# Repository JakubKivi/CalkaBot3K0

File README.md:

# CalkaBot3K0

Całkabot 3k0 is a mini-sumo robot equipped with arms designed to lift the opponent. Taking advantage of the lack of size restrictions after the round begins, this beauty you see in the picture unfolds its lifting arms. In the photo, it's already in the fully deployed position.

More info [here](https://jakubkivi.github.io#portfolio-modal-calk3)

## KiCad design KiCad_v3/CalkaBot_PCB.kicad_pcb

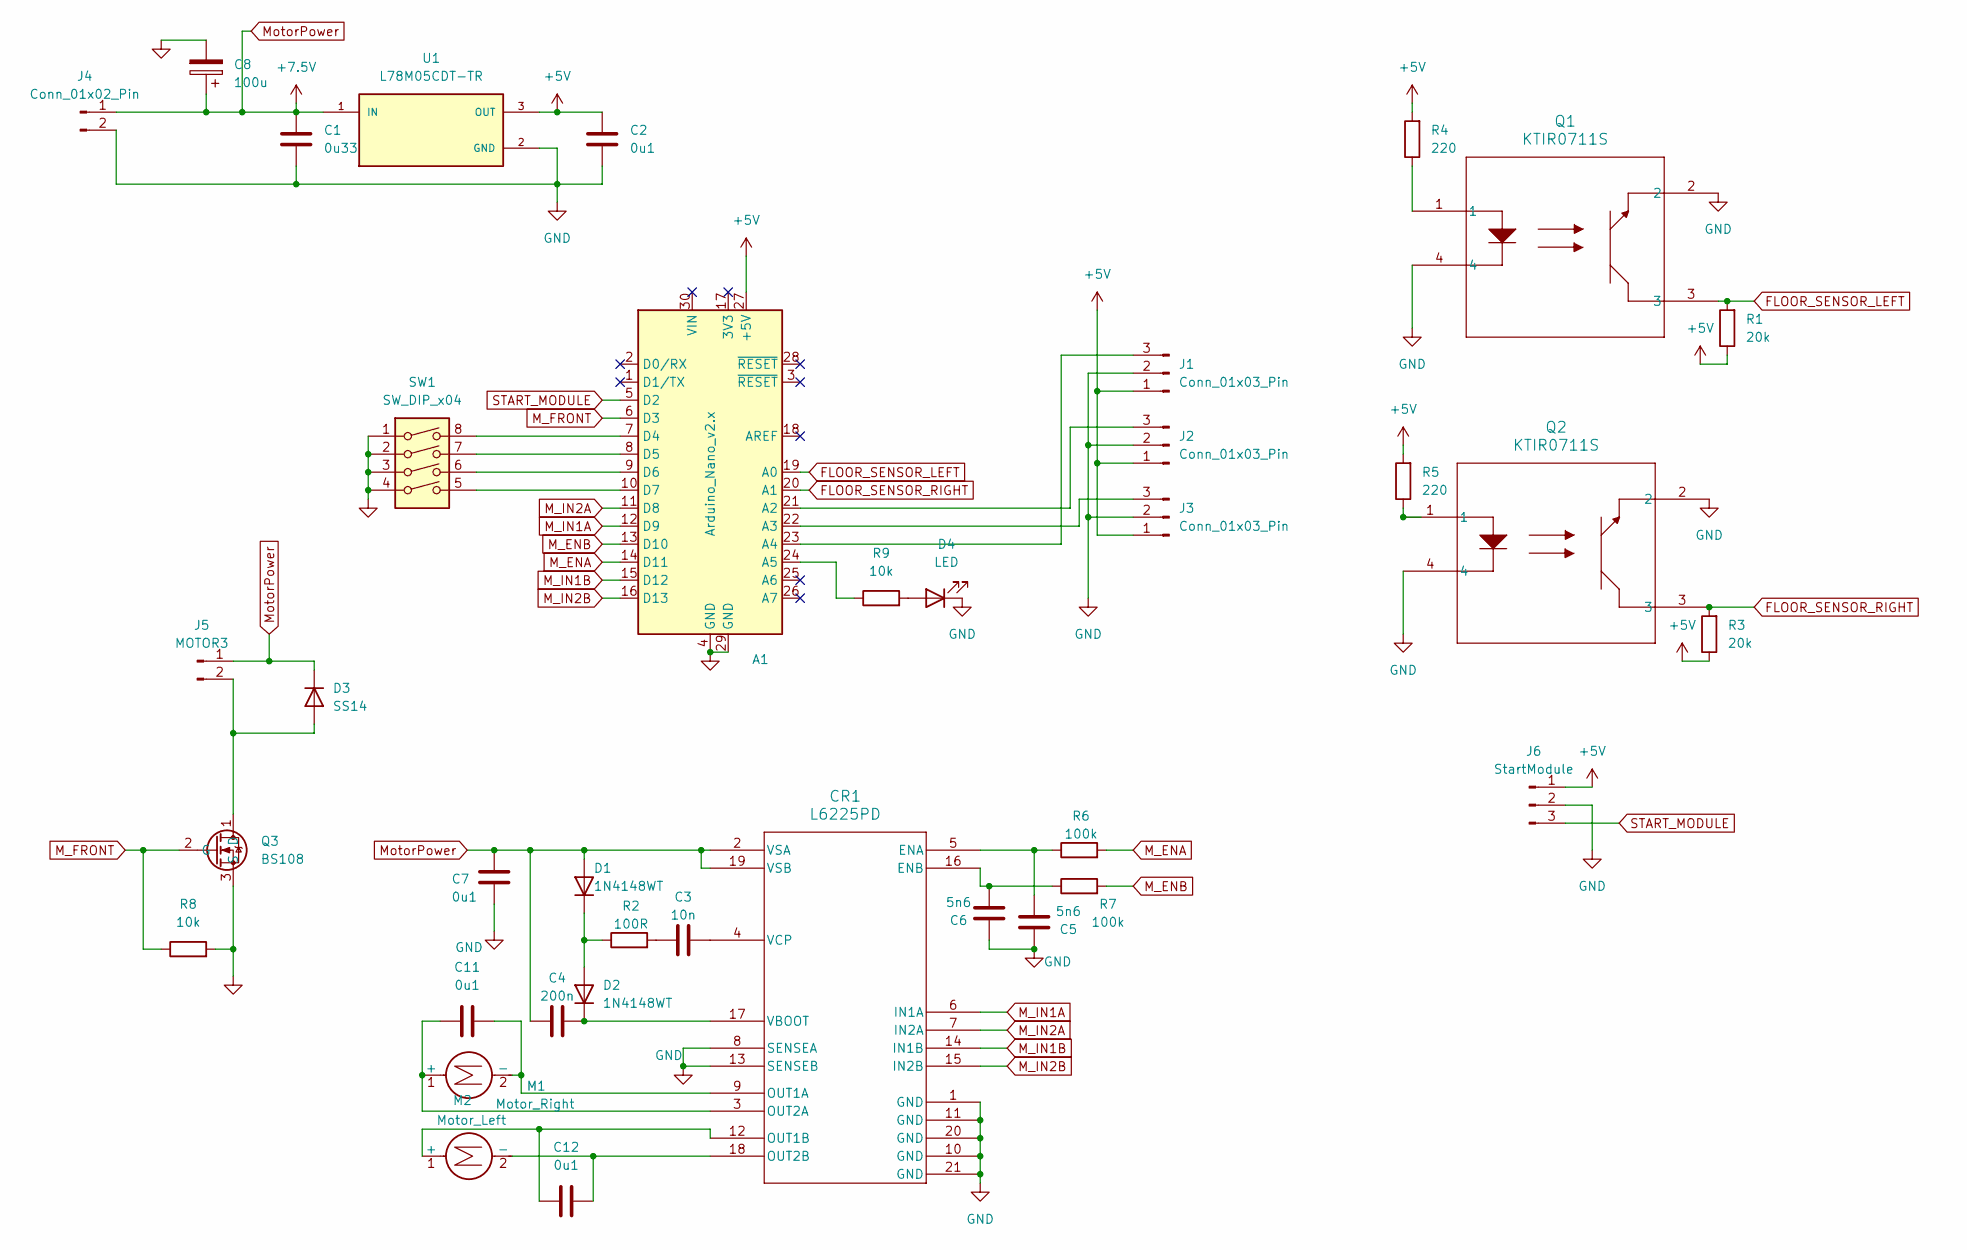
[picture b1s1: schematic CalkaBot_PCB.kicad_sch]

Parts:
A1: Arduino_Nano_v2.x; Arduino_Nano
C1: 0u33; C_0805_2012Metric_Pad1.18x1.45mm_HandSolder
C2, C7, C11, C12: 0u1; C_0805_2012Metric_Pad1.18x1.45mm_HandSolder
C3: 10n; C_0805_2012Metric_Pad1.18x1.45mm_HandSolder
C4: 200n; C_0805_2012Metric_Pad1.18x1.45mm_HandSolder
C5, C6: 5n6; C_0805_2012Metric_Pad1.18x1.45mm_HandSolder
C8: 100u; CP_Elec_6.3x7.7
CR1: L6225PD
D1, D2: 1N4148WT; D_SOD-123
D3: SS14; D_SMA_Handsoldering
D4: LED; LED_0805_2012Metric_Pad1.15x1.40mm_HandSolder
J1, J2, J3: Conn_01x03_Pin; JST_PH_B3B-PH-K_1x03_P2.00mm_Vertical
J4: Conn_01x02_Pin; PinHeader_1x02_P2.54mm_Vertical
J5: MOTOR3; PinHeader_1x02_P2.54mm_Vertical
J6: StartModule; PinHeader_1x03_P2.54mm_Vertical
M1: Motor_Right; CalkBot3k0_Motor_Right
M2: Motor_Left; CalkBot3k0_Motor_Left
Q1, Q2: KTIR0711S
Q3: BS108; SOT-223-IRLL014NTRPBF
R1, R3: 20k; R_0805_2012Metric_Pad1.20x1.40mm_HandSolder
R2: 100R; R_0805_2012Metric_Pad1.20x1.40mm_HandSolder
R4, R5: 220; R_0805_2012Metric_Pad1.20x1.40mm_HandSolder
R6, R7: 100k; R_0805_2012Metric_Pad1.20x1.40mm_HandSolder
R8, R9: 10k; R_0805_2012Metric_Pad1.20x1.40mm_HandSolder
SW1: SW_DIP_x04; SW_DIP_SPSTx04_Slide_9.78x12.34mm_W7.62mm_P2.54mm
U1: L78M05CDT-TR; VREG_L78M05CDT-TR; PARTREV 24

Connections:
+5V: A1.27 (+5V), C2.1, J1.1, J2.1, J3.1, J6.1, R1.1, R3.1, R4.2, R5.2, U1.3 (OUT)
FLOOR_SENSOR_LEFT: A1.19 (A0), Q1.3, R1.2
FLOOR_SENSOR_RIGHT: A1.20 (A1), Q2.3, R3.2
GND: A1.4 (GND), A1.29 (GND), C1.2, C2.2, C5.1, C6.1, C7.2, C8.2, CR1.1 (GND), CR1.8 (SENSEA), CR1.10 (GND), CR1.11 (GND), CR1.13 (SENSEB), CR1.20 (GND), CR1.21 (GND), D4.1 (K), J1.2, J2.2, J3.2, J4.2, J6.2, Q1.2, Q1.4, Q2.2, Q2.4, Q3.3 (S), R8.2, SW1.1, SW1.2, SW1.3, SW1.4, U1.2 (GND); also elsewhere on the board
M_ENA: A1.14 (D11), R6.2
M_ENB: A1.13 (D10), R7.2
M_FRONT: A1.6 (D3), Q3.2 (G), R8.1
M_IN1A: A1.12 (D9), CR1.6 (IN1A)
M_IN1B: A1.15 (D12), CR1.14 (IN1B)
M_IN2A: A1.11 (D8), CR1.7 (IN2A)
M_IN2B: A1.16 (D13), CR1.15 (IN2B)
MotorPower: C1.1, C4.1, C7.1, C8.1, CR1.2 (VSA), CR1.19 (VSB), D1.2 (A), D3.1 (K), J4.1, J5.1, U1.1 (IN); also elsewhere on the board
unnamed: A1.21 (A2), J2.3
unnamed: A1.22 (A3), J3.3
unnamed: A1.23 (A4), J1.3
unnamed: A1.24 (A5), R9.1
unnamed: A1.7 (D4), SW1.8
unnamed: A1.8 (D5), SW1.7
unnamed: A1.9 (D6), SW1.6
unnamed: A1.10 (D7), SW1.5
unnamed: C3.1, R2.2
unnamed: C5.2, CR1.5 (ENA), R6.1
unnamed: C6.2, CR1.16 (ENB), R7.1
unnamed: C11.1, CR1.9 (OUT1A), M1.2 (-)
unnamed: C12.2, CR1.12 (OUT1B), M2.1 (+)
unnamed: C11.2, CR1.3 (OUT2A), M1.1 (+)
unnamed: C12.1, CR1.18 (OUT2B), M2.2 (-)
unnamed: C4.2, CR1.17 (VBOOT), D2.1 (K)
unnamed: C3.2, CR1.4 (VCP)
unnamed: D1.1 (K), D2.2 (A), R2.1
unnamed: D3.2 (A), J5.2, Q3.1 (D)
unnamed: D4.2 (A), R9.2
unnamed: Q1.1, R4.1
unnamed: Q2.1, R5.1
START_MODULE: A1.5 (D2), J6.3

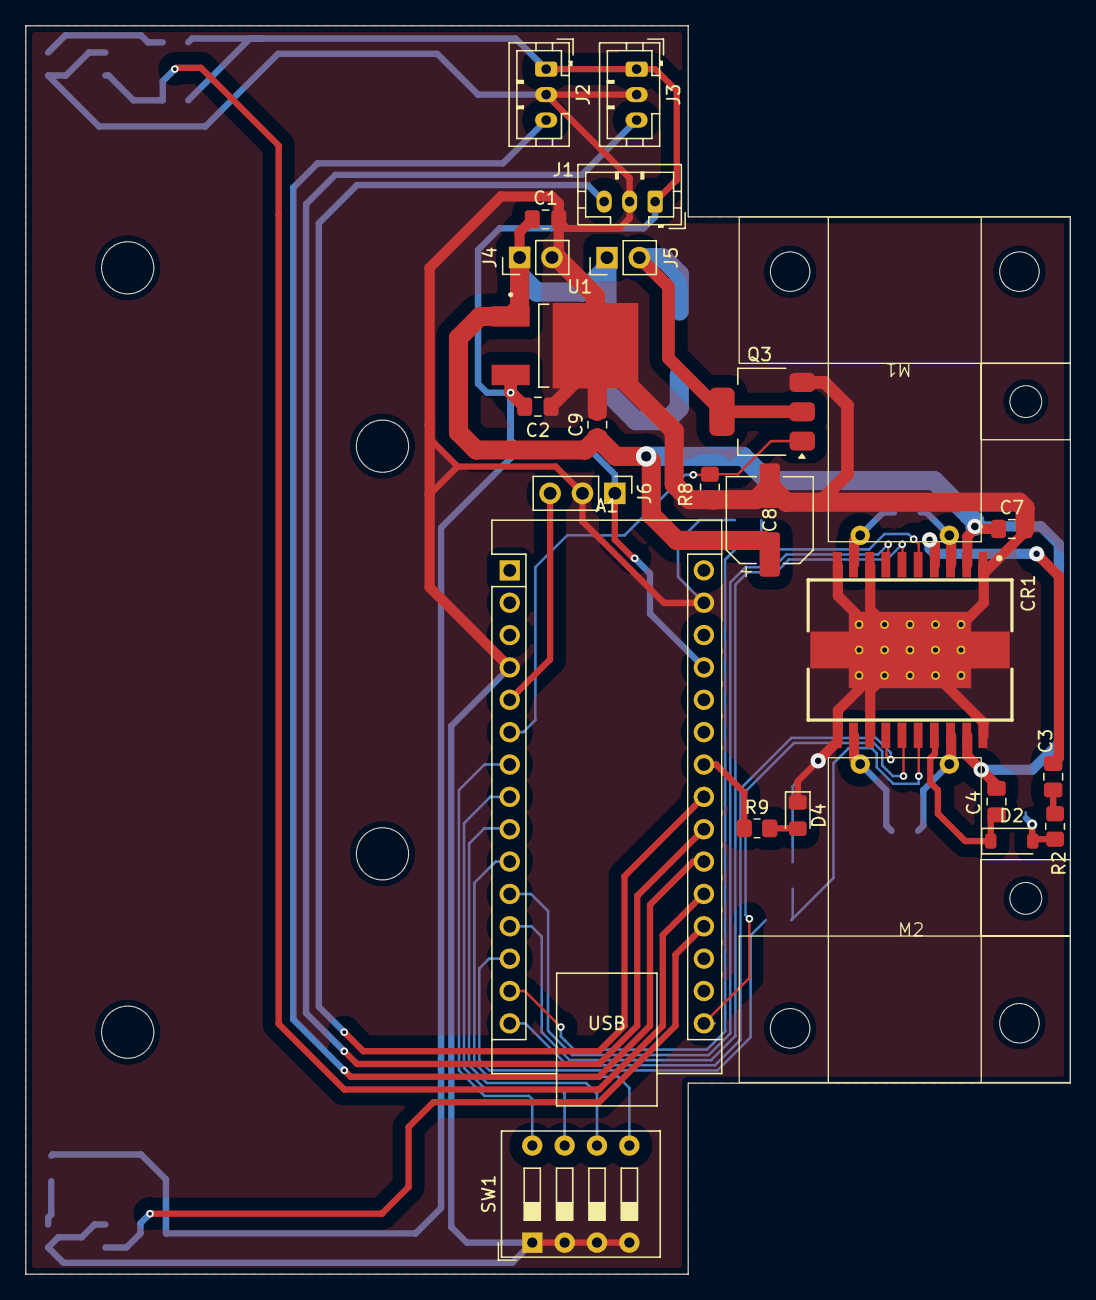
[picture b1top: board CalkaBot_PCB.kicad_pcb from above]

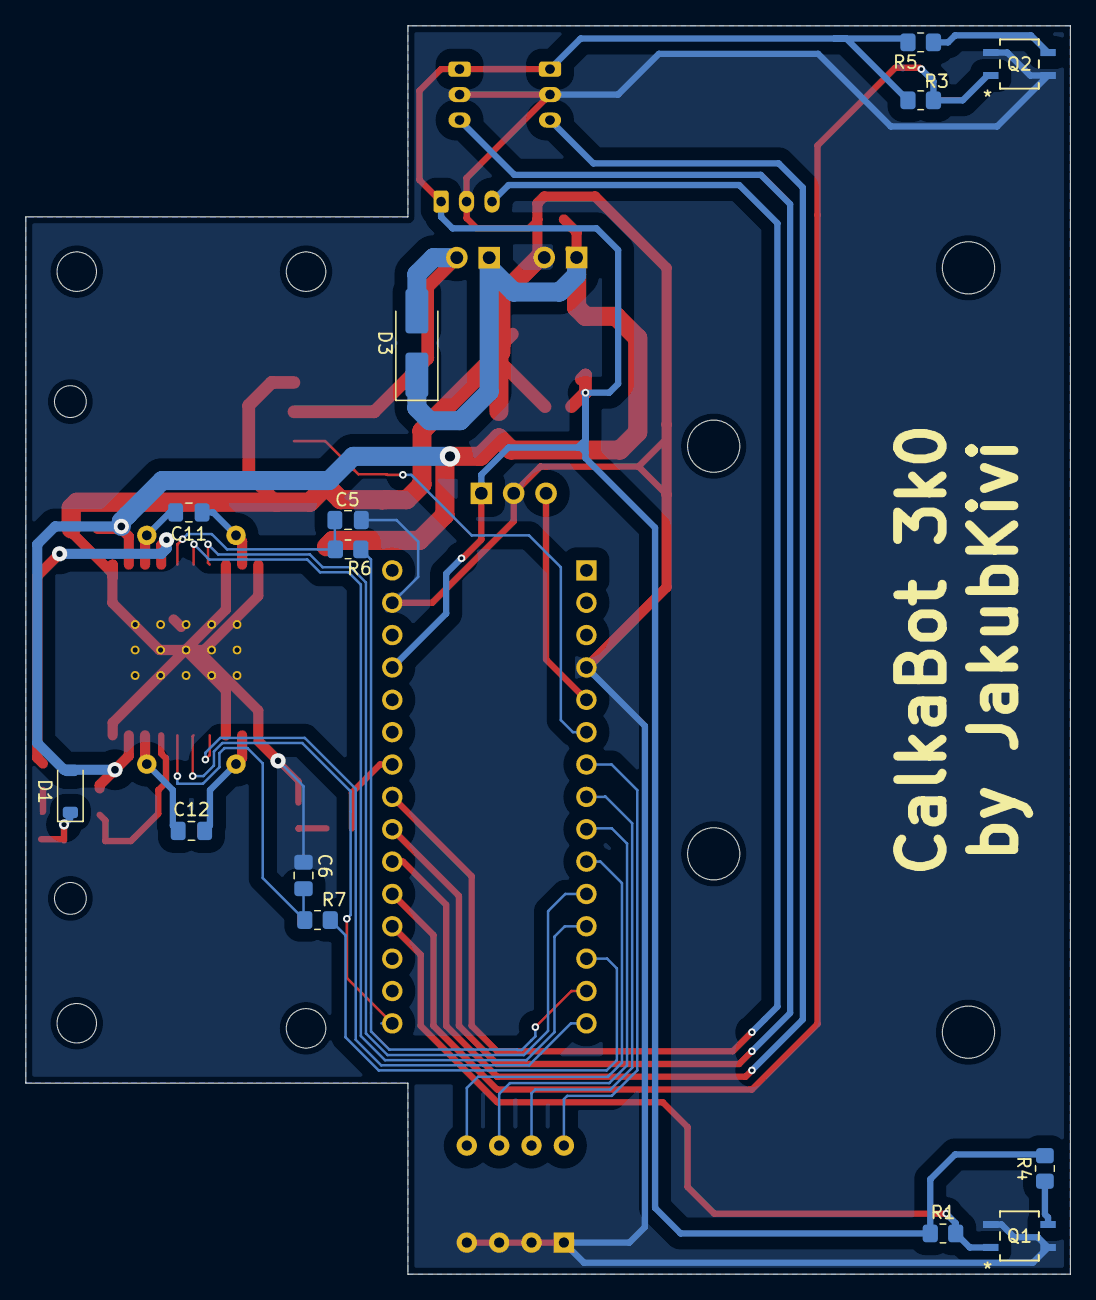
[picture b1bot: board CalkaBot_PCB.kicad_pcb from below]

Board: 2 copper layers, 82.0 x 98.0 mm, 39 parts (14 on the bottom side), 35 nets.

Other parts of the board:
C9: 0u1; C_0805_2012Metric_Pad1.18x1.45mm_HandSolder

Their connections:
GND: C9.2; also elsewhere on the board
MotorPower: C9.1; also elsewhere on the board

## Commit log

2024-04-02 obudowa silnika done
2024-04-03 Trzymajka na sharpa
2024-04-05 ręka usprawniona, spychacz rozppoczęty
2024-04-15 front sharp connected, setting angle
2024-04-29 bateria i dupa
2024-05-06 zostaly śrubki chyba
2024-05-07 zostaly srubki i klapka z tylu?
2024-05-20 z starego pc
2024-05-22 updated NX, almost finished, created KiCAD project
2024-05-23 finishing NX with screws
2024-06-01 working on screws and holes on pcb
2024-06-03 working on PCB + changes within NX for project review
2024-08-11 w trakcie ukladania elementow
2024-09-30 PCB finished ready to send
2024-10-19 płytka leci a rece sa gotowe do druku
2024-10-19 dobra teraz git xd
2024-10-20 Added ignore, working on software makefiles
2024-10-20 makefile working
2024-10-24 working on soft and 2nd version of board
2024-10-25 continue testing board and making program'
2024-11-01 wyslano druga plytke pisze sie praca i program
2024-11-10 fixed pwm and diodes, continue working on program an soldering
2024-11-10 pierdoly
2024-11-16 tested, robot is driving
2024-11-18 migrated to platformIO waiting for print, everything works
2024-11-20 kodzik na czas drukowania
2025-02-16 Druga płytka działa i jeździ
2025-04-02 Updated Pinout with NEW MOTOR after incidento mucho klojegwinto xd
2025-04-03 laptop configuring
2025-04-03 Working code for EastRobo vThursday
2025-04-04 Final adjustments in turns. Friday
2025-04-09 poprawki przed rybnikiem
2025-04-10 strategia machania dupciom, oponka no i ogólnie rybnik nasz essa
2025-04-11 ręka urwana psych lekki przykląk, co bedzie to bedzie
2025-04-11 config przed rybnikiem
2025-04-12 stare z laptopa
2025-04-13 CalkaBot 3k0 done?
2025-04-13 added image
2025-04-13 tera to nie wiem o co mu chodzi
2025-04-13 assets folder renamed
